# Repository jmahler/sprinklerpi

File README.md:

## NAME

SprinklerPI - Web based sprinkler control system running Linux.

## DESCRIPTION

- web based
- sprinkler control system
- modular software design
- modular hardware design
- expandable from 1 to 24 valves

SprinklerPI is a web based sprinkler control system running Linux.

Schedules can be created to run valves at some day and time during the week.
There is no limit to the size, complexity, or number of schedules.
The web interface is designed to be simple and easy to use.

The hardware is modular and can be scaled to the size of a particular
situation.  Each control/driver module can drive eight valves and there
can be from one to three of these modules allowing for a maximum of
24 valves.  Expansion is accomplished using a SPI bus with a daisy
chain configuration.

The controller runs Linux on a [RasberryPI][rpi].
Both [Nginx][nginx] and [Apache][apache] web servers are supported
and they can be installed directly on the RasberryPI.
The web interface is written in [PHP][php] which one of the most
commonly used languages for constructing web interfaces.

  [rpi]: http://www.rasberrypi.org
  [PHP]: http://www.php.net

The software architecture is designed to be simple and maintainable.
All programs (daemons, web interface) communicate with each other
using a set of human readable text files.  And each daemon is designed
to do one task and do it well.

For example, when the web interface modifies a schedule, the schedule
daemon, which is watching the schedule file, notices this change and
updates its schedules.  When an entry in a schedule becomes due the
schedule daemon adds it to the queue.  A queue is used because not
all valves can be on at the same time.  The queue daemon manages
the queue and decides which valves to turn on so that no jobs are lost.
Finally, the watering daemon watches the valve files and physically
turns on valves.  And all of these files can be viewed and edited from
the command line which simplifies debugging.

     daemons:  www   scheduled  queued   waterd
                 \     /   \     /  \     /  \
                  \   /     \   /    \   /    \
       files:    schedule   queue    valves  (device)

## CONTENTS

There are various components in this project.  Each in located in its
own directory as described below.

  src/ - All source code and daemons.

  doc/ - All documentation including: design manual, testing manual, etc.

  doc/sprinklerpi-files.zip - An example set of SprinklerPI files.
	Both the web interface and daemons read and modify these files.

  etc/ - Configuration files, init.d scripts, and web server configuration
	examples.

  pcb/ - Printed circuit board (PCB) designs using [Kicad][kicad].

  www/ - Web interface written in [PHP][php].

  [kicad]:http://www.kicad.org

  [php]:http://www.php.net

  [nginx]:http://www.nginx.org

  [apache]:http://www.apache.org

## SYSTEM SETUP

The system requires certain packages to be installed.

Since some of the daemons are written in [Perl][perl], several
libraries must be installed.  Specifically YAML::Syck and Linux::Inotify2.

  [perl]:http://www.perl.org

Under [Debian][deb] Linux packages are available for installation.

  [deb]:http://www.debian.org

    $ apt-get install libyaml-syck-perl
    $ apt-get install liblinux-inotify2-perl

Under [Redhat][rpm] these can be installed using `yum install <pkg>`.

  [rpm]:http://www.redat.com

    $ yum --enablerepo=rpmforge --enablerepo=atomic install perl-YAML-Syck
    $ yum --enablerepo=rpmforge --enablerepo=atomic install perl-Linux-Inotify2

If the packages are not available in [Redhat][rpm] the `cpan` command
can be used.

    $ cpan -i Linux::Inotify2

At this point, with the Perl libraries installed, it should be possible to run
the queue daemon (`spkpi-queued`), and the scheduler daemon
(`spkpi-scheduled`).

The final daemons needed to get the system working are the water
daemon (`spkpi-waterd`) which depends on the `water` command and/or
the client/server daemons.  These are written in C and must be compiled.
To build these change to the root of the project and type `make`,
this will build the library.

    $ make

Then change to the binary directory and type `make` again, this
will build the executables.

    $ cd bin/
    $ make

Depending on whether this system is using a client/server or installed
directly on the device will determine what can be compiled.
For example, the `water` command cannot be compiled on systems without
SPI headers.  For a server only system just make the server.

    $ make spkpi-waterd-server

The final step in setting up the system is configuring the web server.
The YAML libraries that [PHP][php] depends on are taken care of during
the previous instructions.  However, the PHP version of YAML must
still be installed.

  [php]:http://www.php.net

The `pecl` command can be used to install the PHP library.
It should build without error if libyaml libraries were correctly installed
previously.

    $ pecl install yaml

If [Nginx][nginx] is being used as the web server several additional packages
need to be installed.

    $ apt-get install php5-fpm php5-cgi

The `extension=yaml.so` option should be added to `/etc/php5/fpm/php.ini`.
To make debugging easier it is helpful to set "display_errors = On" as well.

A similar configuration must be performed when using [Apache][apache].

Then, after restarting the web server, it should be setup and ready to run.

    $ service php5-fpm restart
    $ service nginx restart

or

    $ service apache2 restart

## SITE SETUP

The system should be setup and have all the necessary libraries
in order to run.  But the location of the html and [PHP][php] files
still needs to be configured.

The files in this project under `www/` are for a web interface.
The web server being used should be configured so that
the site root is `www/html`.  An example configuration
for [Nginx][nginx] is in `etc/nginx`.  A similar configuration
can be created for Apache.

Since the web server must be able to modify the sprinklerpi
files the permissions must be correct.  If the web server is
running as the user `www-data` that user/group should have
read/write access to the files.

    $ sudo chown -R :www-data sprinklerpi/
    $ sudo chmod -R g+w sprinklerpi/

The `_config.inc` is where the site is configured.

    www/html/_config.inc

## STARTUP, /etc/init.d/

Depending upon how this system is being used, different daemons
will need to be started.  A set of startup scripts are provided in
`/etc/init.d/` for each of the situations.

The init scripts expect a basic configuration to be present in

    /etc/default/sprinklerpi

otherwise they will use default values which may not work.
This file can either be copied or a symbolic link can be created.

    $ sudo ln -s /home/jeri/sprinklerpi/etc/default/sprinklerpi \
        /etc/default/sprinklerpi

This default configuration defines values such as the location of
the sprinklerpi files and binaries.

Once this is completed the scripts can be used to start the daemons.

    $ sudo etc/init.d/spkpi-waterd start
    $ sudo etc/init.d/spkpi-scheduled start
    $ sudo etc/init.d/spkpi-queued start

## FAQ

Q. Why does this design use files to communicate between daemons
and the web server?  Doesn't this make it more complex?

A. There are several reasons why a file system interface was used:

  - transparent - The files can be viewed using standard command
  line tools (`cat`).  This makes it simple to verify the operation
  of a daemon, web interface or any other program.

  - debugging - The files can be viewed and modified using standard
  command line tools and this makes it is easy to test and verify
  operation.

  - security - The daemons which control watering need permissions to
  write to the SPI device.  But the web server and other user
  programs don't since these use the files.  This reduces the
  potential magnitude of any privilege escalation bugs.

  - history - The current state of the system can be saved by
  simply saving the files.
  A version control system such as [Git][git] can even
  be used to record the history.

  - interoperable - Any program in any language can interface files
  and no special libraries are required.
  This system uses programs written in C, Perl, PHP, and they all
  communicate with each other using these files.

  - One alternative would be to use sockets.
  This would allow communication between daemons.
  But the state of the system cannot be easily examined.
  Also, the state cannot be saved unless it is dumped to some
  intermediate format.
  Sockets programming is also more complex than file operations.

  - Another alternative is to create a monolithic program which does
  everything.  This shares all the shortcomings of a socket interface.
  And since the system is not modular it is also difficult to debug.

  [git]:http://git-scm.org

Q. Schedules with lots of entries (1000+) get cutoff after making
changes through the web interface.

A. There is a maximum number of POST variables that PHP will allow before
it rejects the submission.  This is likely being exceeded.
To confirm the problem the server error.log should be checked.

To get an idea of the magnitude of this form suppose every minute
each group has a new entry (3) and this is over twelve hours
(12 x 60 x 3 = 2160).  Now for each entry in the schedule there are
six columns (2160 x 6 = 12960).

To fix the problem increase the value of `max_input_vars` in php.ini.

    ; php.ini
    max_input_vars = 15000

Q. Why does wifi sporadically go down when using a Ralink based USB wifi
adapter?

A. This is a known issue with the drivers on a RasberryPI.
By connecting using the Ethernet port the wifi interface can be brought
back up.

    $ sudo ifup wlan0

But the most reliable solution is to use Ethernet instead of wifi.

## AUTHOR

Jeremiah Mahler <jmmahler@gmail.com><br>
<http://github.com/jmahler>

## COPYRIGHT

Copyright &copy; 2014, Jeremiah Mahler All Rights Reserved.<br>
This project is free software and released under
the [GNU General Public License][gpl].

  [gpl]: http://www.gnu.org/licenses/gpl.html

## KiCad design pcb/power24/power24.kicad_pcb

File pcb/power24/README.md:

NAME
----

sprinklerpi/pcb/power24

DESCRIPTION
-----------

This directory contains the power supply module PCB.

A list of parts needed to assemble this module is included.
It is in csv format which can be uploaded to the bill of materials (BOM)
manager in Digi-Key.  In some cases Digi-Key is a bit finicky so minor
alterations to the .csv may be required.

    power24-parts.csv

The PCB was designed using the 2013-jul-07 version of [Kicad][kicad].
To open the project open the power24.pro file.
The other files (power24.sch, power24.kicad_pcb, etc) will be available
from this project.

  [kicad]: http://www.kicad-pcb.org/

The Gerber files which are generated from PCB in Kicad are also included.

    power24-F_Cu.gtl
    power24-B_Cu.gbl
    power24-F_Mask.gts
    ...
  
A script is also included (package-gerbers.sh) in the parent directory
which will automatically packages these so they can be sent to
[Osh Park][osh] to be manufactured.

    $ ../package-gerbers.sh power24

  [osh]: http://www.oshpark.com

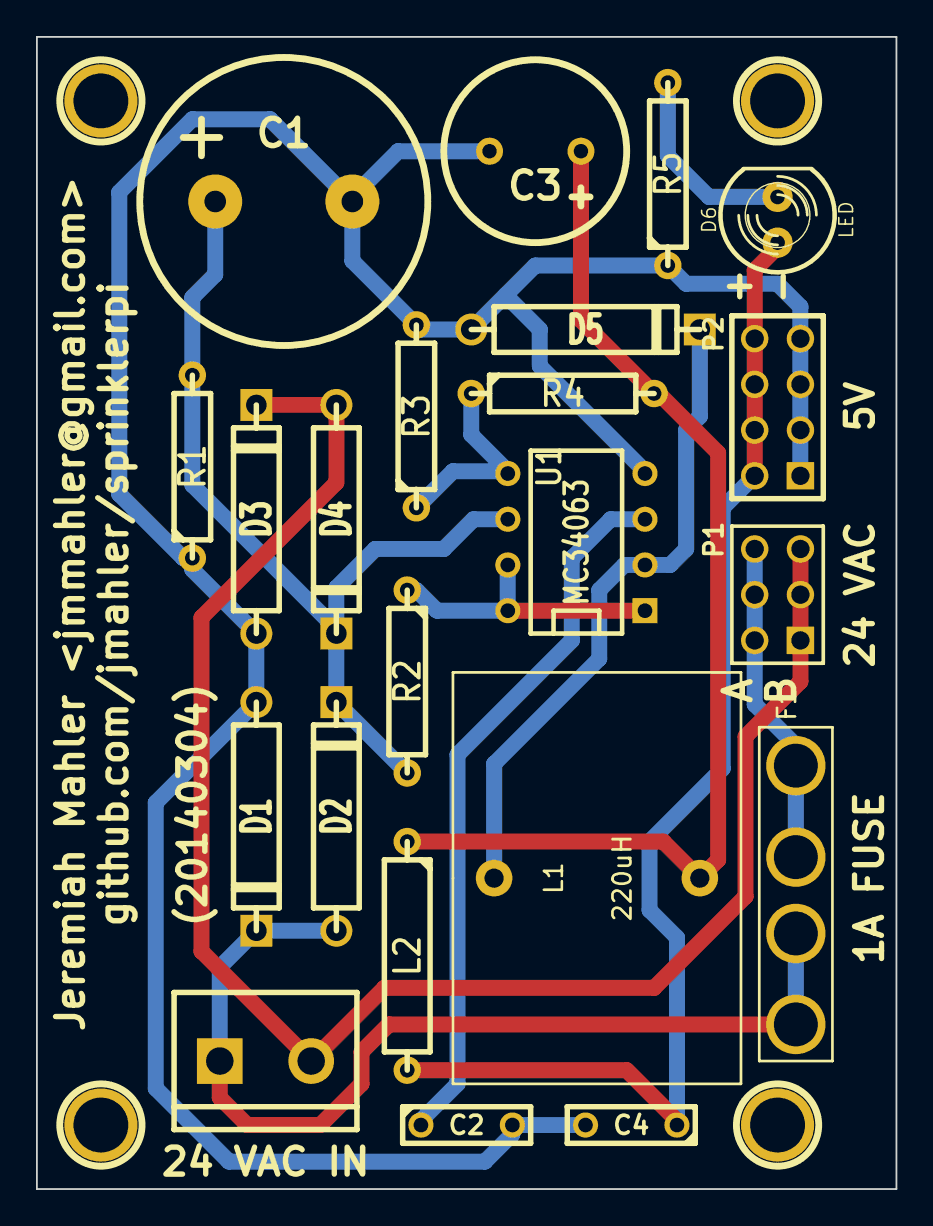
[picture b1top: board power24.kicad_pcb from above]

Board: 2 copper layers, 47.8 x 64.0 mm, 26 parts (0 on the bottom side), 12 nets.

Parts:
1PIN, 1PIN#2, 1PIN#3, 1PIN#4: P***; 1pin
C1: 2200 uF; Elko_vert_DM16_RM7-5_CopperClear
C2: 1000 pF; C2
C3: 180 uF; Elko_vert_DM10_RM5_CopperClear
C4: 1.0 uF; C2
D1, D2, D3, D4: DIODE; D5
D5: 1N5819; D5
D6: LED; LED-5MM
F1: 1A; FUSE_HOLDER_100057
L1: 220uH; INDUCTOR_TORROID_VERT_086
L2: 1.0 uH; R5
P1: CONN_3X2; pin_array_3x2
P2: CONN_4X2; pin_array_4x2
P3: CONN_2; bornier2
R1: 0.5M; R4
R2: 0.25; R4
R3: 3k; R4
R4: 5k; R4
R5: 330; R4
U1: MC34063; DIP-8__300

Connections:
GND: C1.2, C2.2, C3.2, C4.2, D1.1, D3.1, D5.1, P2.1, P2.3, P2.5, P2.7, R1.1, R3.2, R5.1, U1.4
unnamed: F1.2, P1.2, P1.4, P1.6
unnamed: D6.2, R5.2
unnamed: C4.1, D6.1, L2.2, P2.2, P2.4, P2.6, P2.8
unnamed: D1.2, D2.1, F1.1, P3.1
unnamed: R2.1, U1.1, U1.7, U1.8
unnamed: D3.2, D4.1, P1.1, P1.3, P1.5, P3.2
unnamed: C1.1, D2.2, D4.2, R1.2, R2.2, U1.6
unnamed: C2.1, U1.3
unnamed: R3.1, R4.1, U1.5
unnamed: D5.2, L1.1, U1.2
unnamed: C3.1, L1.2, L2.1, R4.2

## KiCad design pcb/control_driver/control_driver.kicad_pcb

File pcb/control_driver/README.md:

NAME
----

sprinklerpi/pcb/control_driver

DESCRIPTION
-----------

This directory contains the control driver PCB.

A list of parts needed to assemble this module is included.
It is in csv format which can be uploaded to the bill of materials (BOM)
manager in Digi-Key.  In some cases Digi-Key is a bit finicky so minor
alterations to the .csv may be required.

    control_driver-parts.csv

The PCB was designed using the 2013-jul-07 version of [Kicad][kicad].
To open the project open the control_driver.pro file.
The other files (control_driver.sch, control_driver.kicad_pcb, etc)
will be available from this project.

  [kicad]: http://www.kicad-pcb.org/

The Gerber files which are generated from PCB in Kicad are also included.

    control_driver-F_Cu.gtl
    control_driver-B_Cu.gbl
    control_driver-F_Mask.gts
    ...
  
A script is also included (package-gerbers.sh) in the parent directory
which will automatically packages these so they can be sent to
[Osh Park][osh] to be manufactured.

    $ ../package-gerbers.sh control_driver

  [osh]: http://www.oshpark.com

BUGS
----

Version 20140304 of the control/driver PCB has the following bugs:

  1. On power up valve number 1 is on, but all should be off.<br>
     This is caused by faulty clear logic.  When the shift register (74HC194)
     is clear it outputs all zeros to the decoder (74HC238).  All zeros
     and enabled turns on valve one.

  1. Noise on SPI pins causes erratic operation.<br>
     With the SPI pins unconnected any noise, such as from a persons hand,
     will cause all sorts of erratic operation.
     Probably needs a pull down/up resistor.

AUTHOR
------

Jeremiah Mahler <jmmahler@gmail.com><br>
<http://github.com/jmahler>

COPYRIGHT
---------

Copyright &copy; 2014, Jeremiah Mahler All Rights Reserved.<br>
This project is free software and released under
the [GNU General Public License][gpl].

  [gpl]: http://www.gnu.org/licenses/gpl.html

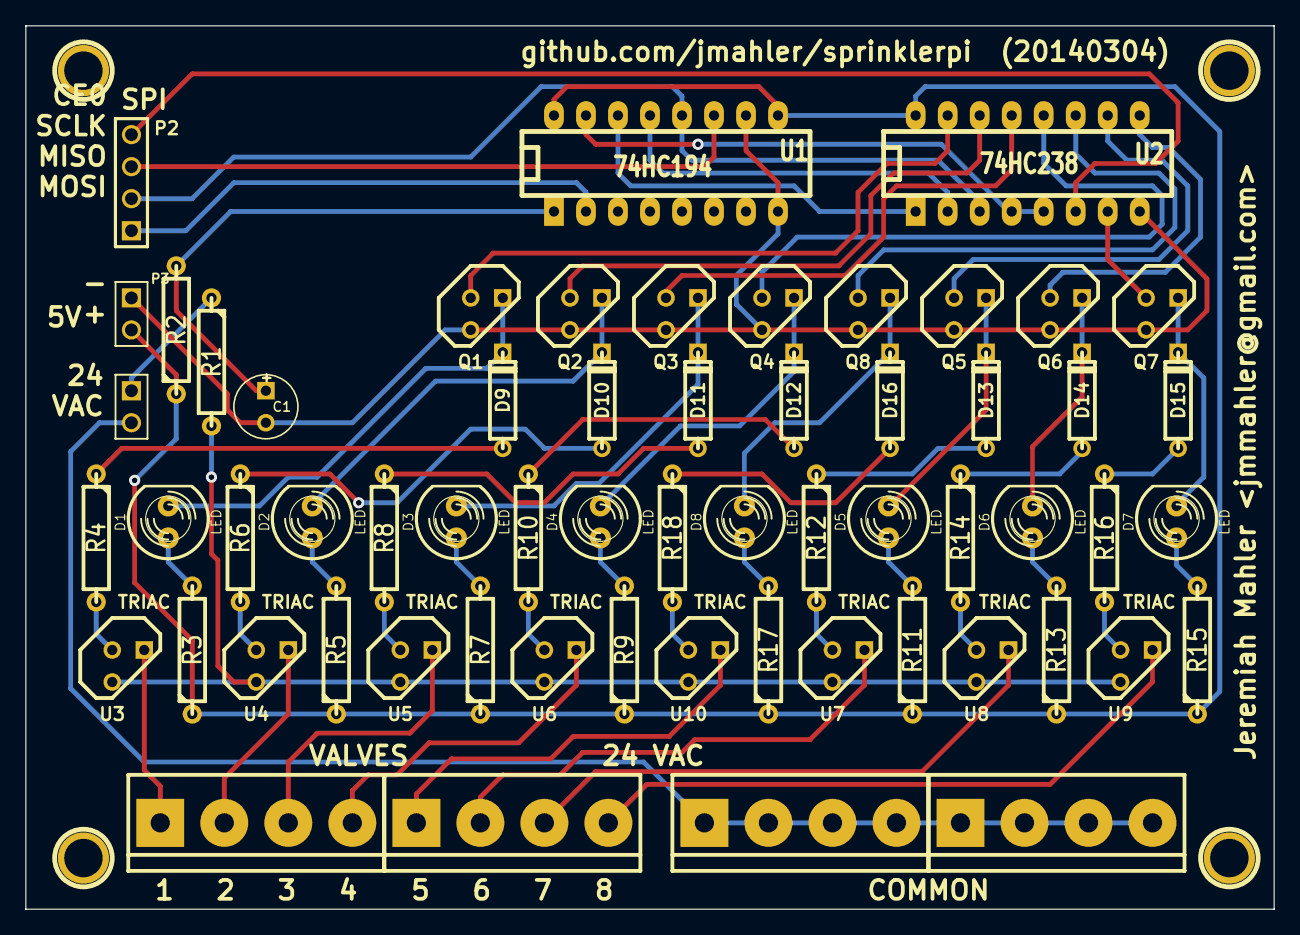
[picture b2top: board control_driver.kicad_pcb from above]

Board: 2 copper layers, 99.1 x 70.1 mm, 64 parts (0 on the bottom side), 61 nets.

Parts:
1PIN, 1PIN#2, 1PIN#3, 1PIN#4: P***; 1pin
C1: 33uF; C1V5
D1, D2, D3, D4, D5, D6, D7, D8: LED; LED-5MM
D9, D10, D11, D12, D13, D14, D15, D16: DIODE; D3
P1, P3: CONN_2; PIN_ARRAY_2X1
P2: CONN_4; PIN_ARRAY_4x1
P4, P5, P6, P7: CONN_4; bornier4
Q1, Q2, Q3, Q4, Q5, Q6, Q7, Q8: MOSFET_N; TO92DGS
R1: 10; R4
R2: 220k; R4
R3, R5, R7, R9, R11, R13, R15, R17: 330; R4
R4, R6, R8, R10, R12, R14, R16, R18: 1k; R4
U1: 74HC194; DIP-16__300_ELL
U2: 74HC238; DIP-16__300_ELL
U3, U4, U5, U6, U7, U8, U9, U10: TRIAC; TO92-132

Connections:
+5V: P3.2, R2.1, R3.1, R5.1, R7.1, R9.1, R11.1, R13.1, R15.1, R17.1, U1.9, U1.16, U2.16
/control/CE0: P2.4, U2.6
/control/MISO: P2.2, U1.12, U2.3
/control/MOSI: P2.1, U1.2
/control/SCLK: P2.3, U1.11
/driver_1/CTL: Q1.G, U2.15
/driver_1/DRV_A: R1.2, U3.2, U4.2, U5.2, U6.2, U7.2, U8.2, U9.2, U10.2
/driver_1/DRV_B: P4.1, U3.1
/driver_2/CTL: Q2.G, U2.14
/driver_2/DRV_B: P4.2, U4.1
/driver_3/CTL: Q3.G, U2.13
/driver_3/DRV_B: P4.3, U5.1
/driver_4/CTL: Q4.G, U2.12
/driver_4/DRV_B: P4.4, U6.1
/driver_5/CTL: Q8.G, U2.11
/driver_5/DRV_B: P5.1, U10.1
/driver_6/CTL: Q5.G, U2.10
/driver_6/DRV_B: P5.2, U7.1
/driver_7/CTL: Q6.G, U2.9
/driver_7/DRV_B: P5.3, U8.1
/driver_8/CTL: Q7.G, U2.7
/driver_8/DRV_B: P5.4, U9.1
GND: C1.2, P3.1, Q1.S, Q2.S, Q3.S, Q4.S, Q5.S, Q6.S, Q7.S, Q8.S, U1.8, U1.10, U2.8
unnamed: P1.1, R1.1
unnamed: P1.2, P6.1, P6.2, P6.3, P6.4, P7.1, P7.2, P7.3, P7.4
unnamed: C1.1, R2.2, U1.1
unnamed: U1.13, U2.2
unnamed: U1.14, U2.1
unnamed: U1.15, U2.4, U2.5
unnamed: D5.2, D13.2, Q5.D
unnamed: D5.1, R11.2
unnamed: D13.1, R12.1
unnamed: R12.2, U7.3
unnamed: R6.2, U4.3
unnamed: D10.1, R6.1
unnamed: D2.1, R5.2
unnamed: D2.2, D10.2, Q2.D
unnamed: D3.2, D11.2, Q3.D
unnamed: R8.2, U5.3
unnamed: D11.1, R8.1
unnamed: D3.1, R7.2
unnamed: D12.1, R10.1
unnamed: R10.2, U6.3
unnamed: D4.2, D12.2, Q4.D
unnamed: D4.1, R9.2
unnamed: D1.1, R3.2
unnamed: D1.2, D9.2, Q1.D
unnamed: D9.1, R4.1
unnamed: R4.2, U3.3
unnamed: D8.1, R17.2
unnamed: D8.2, D16.2, Q8.D
unnamed: D16.1, R18.1
unnamed: R18.2, U10.3
unnamed: R16.2, U9.3
unnamed: D15.1, R16.1
unnamed: D7.2, D15.2, Q7.D
unnamed: D7.1, R15.2
unnamed: D6.1, R13.2
unnamed: D6.2, D14.2, Q6.D
unnamed: D14.1, R14.1
unnamed: R14.2, U8.3

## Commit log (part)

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2013-08-19 start
2013-08-21 switched to Inkscape without LaTeX
    The LaTeX output with Inkscape was neat since
    LaTeX formatting characters could be used. But
    the placement and the font size was different
    than the diagram. The result is easier to control
    using the fonts in the diagram are used.
2013-08-27 added control diagram
    A diagram of the control circuit has been added.
    It includes the SPI to shift register and decoder logic.
2013-12-22 pointed .pdf in README to build branch
2013-12-22 re-factored control circuit to eliminate two chips
    The control circuit has been re-factored to eliminate
    the need for two inverters by using a 74HC238 (3-8 decoder)
    which provides non-inverting outputs. This also changes the
    chips from LS to HC series.
2013-12-24 changed to switched 5V DC regulator
    The 5V DC power supply has been changed to use
    a switching power supply (MC34063A) instead of
    a linear power supply (LM7805) because it is more
    efficient and consumes less power.
2013-12-28 cleaned up 'water' program code
    The command line program 'water' for controlling
    the valves has been cleaned up.
    - better error messages
    - grouped together related code
    - eliminated use of a global variable
    - added more error checking
2014-01-03 documented expansion capabilities
    The system uses SPI to communicate with the control
    groups which allows it to be daisy chained for expansion.
    However the current design is limited to three control
    groups with a single power supply.
2014-01-06 mapped footprints for power supply pcb
    The footprints have been mapped to the schematic
    components for the power supply pcb. An online
    library was found for the Borniers. And "modules"
    for the fuse holder and transformer were created.
2014-01-09 fixed power PCB name on inductor
    The name on the inductor footprint is not
    automatically created correctly. It uses the
    value given in the schematic when I want it to
    use the part id. Fixed by manually editing the
    name.
2014-01-23 added project concept document
2014-01-26 lots of work on the design document
    Lots of work has been done on the design
    document. It was converted over for the
    SprinklerPI project from an old fuel injection
    project. It is not complete and still
    needs some work.
2014-01-27 renamed main.tex to design.tex, concept.tex, etc
2014-02-04 consolidated and revised schedule
2014-02-04 more .gitignores related to LaTeX
2014-02-05 PCB Gerbers created, design sent to Osh Park
    The Gerber files for the power supply have been
    generated and sent to Osh Park to be manufactured.
    It remains to be seen whether any errors arise
    from manufacturing.
2014-02-07 new doc build link
2014-02-11 support for variable number of control groups
    Previously, the water command only supported the control
    of one group. It has now been generalized to support
    any number of control groups.
2014-02-18 added a one page data sheet
2014-03-01 fixed minor power PCB problems
    Fixed several issues with the power PCB.
    - fuse holder
    - increased inner diameter to fix tight fit
    - increased outer diameter to increase pad surface
    - switched terminal connector with larger hole size
    - 1.25 -> 1.54 mm
2014-03-02 control/driver PCB arranged
    All the components for the control/driver PCB have
    been arranged. Next traces need to be added.
2014-03-02 power PCB, expanded 5V to 4-pin
    Previously the 5V output header was
    three pairs of pins. But this would only
    support two control boards and one PI.
    It has been expanded to four to support
    three control boards and one PI.
2014-03-02 increased power CT capacitor size
    It was determined that when the DC source
    voltage is low (13.8 volts instead of 17 volts)
    the MC34063 will regulate the output voltage
    using a higher frequency. And since a relatively
    large inductor (L1, 220 uH) is being used this
    can create a substantial voltage drop (1.5 V).
2014-03-03 removed left over wire terminator
    Removed a left over wire terminator from the
    control PCB at the entry to the shift register.
2014-03-03 generated Gerbers for control_driver and power24 PCBs
2014-03-04 cleaned up Makefiles to package Gerbers
2014-03-05 PCB makefile now depends on Gerber files
    Now, when the Gerber files are updated, the Makefile
    will know to repackage the .zip.
2014-03-17 added PCB images to power supply testing instructions
2014-03-20 encode_cmd buffer fix, printf, spidev0.0
    The encode_cmd returns a pointer to a buffer.
    But this buffer was an automatic variable so
    invalid values were being produced.
    Fixed by making it static.
    Added a cast to printf to quiet warnings
    about size_t with %lu.
2014-03-20 fixed valve 8 bug
    The encode command checked that the valve number was from zero to 7.
    But the commands are 0 for all off and 1 through 8 for valves.
    Fixed command to allow valve 8 as well.
2014-03-22 notes on MC34063 operating frequency
2014-03-22 encode_cmd() verified with 3 controllers
    The encode_cmd() which converts the command string
    to bytes to be written over SPI has been verified
    with three controllers. Both the nibbles in a byte
    and the byte order had to be changed.
2014-03-24 re-ordered control_driver parts for assembly
    The control_driver parts list has been placed in
    order according to the parts that would be installed
    in to the PCB first.
2014-03-25 added a technology roadmap
2014-04-01 revised project schedule
    The project schedule has been revised to account
    for the problems that were encountered (power 5V 3.3V).
    The remaining tasks are all software related.
2014-04-13 added a water-demo.pl program
    A demonstration program has been added that
    operates the the valves (LEDs) in all sorts
    of entertaining patterns.
2014-04-15 added html DOCTYPE
2014-04-15 cleaned up program docs, added copyrights
    The documentation has been cleaned up in all
    of the programs and appropriate copyright
    notices (GPL) have been added.
2014-04-16 added 'off' mode to dispatch
2014-04-18 added spkpi-manual daemon
    A daemon has been created for the manual mode.
    It monitors the manual/ valve files and runs
    the water command when they change.
2014-04-19 added FAQ with a file system design question
2014-04-20 separated mode codes in to own files
    The PHP code for different modes has been separated
    in to its own files which are then included by index.php.
2014-04-20 added "schedule" mode, found errmsg bug
    With the "schedule" mode an error is generated
    because it is not supported by the library.
    But this error was not being displayed because
    the wrong $spkpi object was being used. The error
    was for the $new_spkpi object but the error message
    was retrieved from $spkpi.
2014-04-22 schedule web interface working
    A working web interface to the scheduler has
    been constructed. Schedules can be edited and
    entries can be added or deleted. It supports
    multiple schedules each of which can be enabled
    or disabled.
2014-04-23 queue daemon working
    The queue daemon (spkpi-queued), which monitors the queues
    and writes the valve file to turn on the valve, is working.
    The design changed from a single queue file for all the groups
    to separate queues for each group. This simplified processing.
2014-04-23 fixed schedule disabled update bug
    Fixed bug where the select menu was using an out
    of date schedule after an update which was causing
    it to display the incorrect enabled/disabled state.
2014-04-23 format schedule time with zeros
    Now the schedule start time and run time will be
    formatted correctly if a partial value is entered
    (e.g. "5:0" -> "05:00").
2014-04-24 spkpi-queued not turning off valves
    Fixed bug in spkpi-queued which caused it to
    not turn off the valves when the time expired.
2014-04-24 spkpi-demo now follows mode
    Now the demo (spkpi-demo) will only run when the mode is 'demo'.
2014-04-24 avoid running as root by adding --chuid to init.d
2014-04-26 switch to off mode turns valves off
    Now when the mode is switched to off the valves will be turned off.
2014-04-26 improved wrapper bin path
    The wrappers will now work either from the command line or
    from an init.d script with $BIN defined.
2014-04-26 mode program configuration obsolete
    With the removal of the dispatch daemon the mode configuration
    is obsolete so it has been removed from sprinklerpi.conf.
2014-04-27 added removed YAML::Syck from spkpi-scheduled
    The YAML::Syck library was incorrectly removed during
    recent changes causing LoadFile to fail. Re-added.
2014-04-27 added very large test schedule and generator
2014-04-27 rewrote README
    The README has been completely re-written.
    The introduction has been expanded to detail the
    features a user of this system would be interested in.
    More setup and install issues have been documented.
2014-04-28 client now turns all valves off during startup
2014-04-28 fixed suggested date, 24 hr format instead of 12 hr
    The suggested date for a new schedule should have
    been in 24 hr format instead of 12 hr format.
2014-04-29 revised README schedule description
2014-05-02 started re-writing test procedures
    Started re-writing the test procedures to be
    more concise and effective. Much work is still
    left and pictures also need to be added.
2014-05-03 Referenced project README for networking configuration
    Documentation for how to setup the software and networking
    is given in the project README so references have been
    added describing this.
2014-05-03 added queueing and concurrent test schedules
2014-05-03 continued documenting web server install
2014-05-04 improved error messages and YAML emit fails
2014-05-04 $cfg->{verbose} must preceed functions that use it
2014-05-05 consistent title page style on all documents
2014-05-05 revised datasheet and requirements
2014-05-05 added more verbose output to spkpi-waterd-server
2014-05-05 fixed diagram lines to valves in overview
2014-05-06 updated architecture diagram in datasheet
2014-05-06 added post board pages
    Added a bunch of pages that can be used to create a poster board.
2014-05-07 added property managers to the list of product users
    Property managers are another potential user of this system.
    Being able to access the sprinkler controls remotely can
    be helpful if the tenants have a problem.
    (suggested by Norm Galassi)
2014-05-16 central doc/ Makefile, preserve .pdf
    A central Makefile has been added in the doc/ directory
    which can be used to build all documents.
    A make clean now leaves behind the .pdf files.
    This is useful when this project is packaged up for someone
    that doesn't have a computer where they can be LaTeX files.
2014-05-16 reviewed concept doc, minor fixes
2014-05-16 minor clarifications in technology roadmap
2014-07-07 rectifier capacitor 20V -> 50V
    The rectifier capacitor had a spec of 20V which was correct when 12 VAC
    was being rectified.
    Vp = Vrms*sqrt(2)
    = 12*sqrt(2)
    = 16.971
    16.971 * 1.10 = 18.668 < 20
2014-10-26 removed unused $sched_dir variable
